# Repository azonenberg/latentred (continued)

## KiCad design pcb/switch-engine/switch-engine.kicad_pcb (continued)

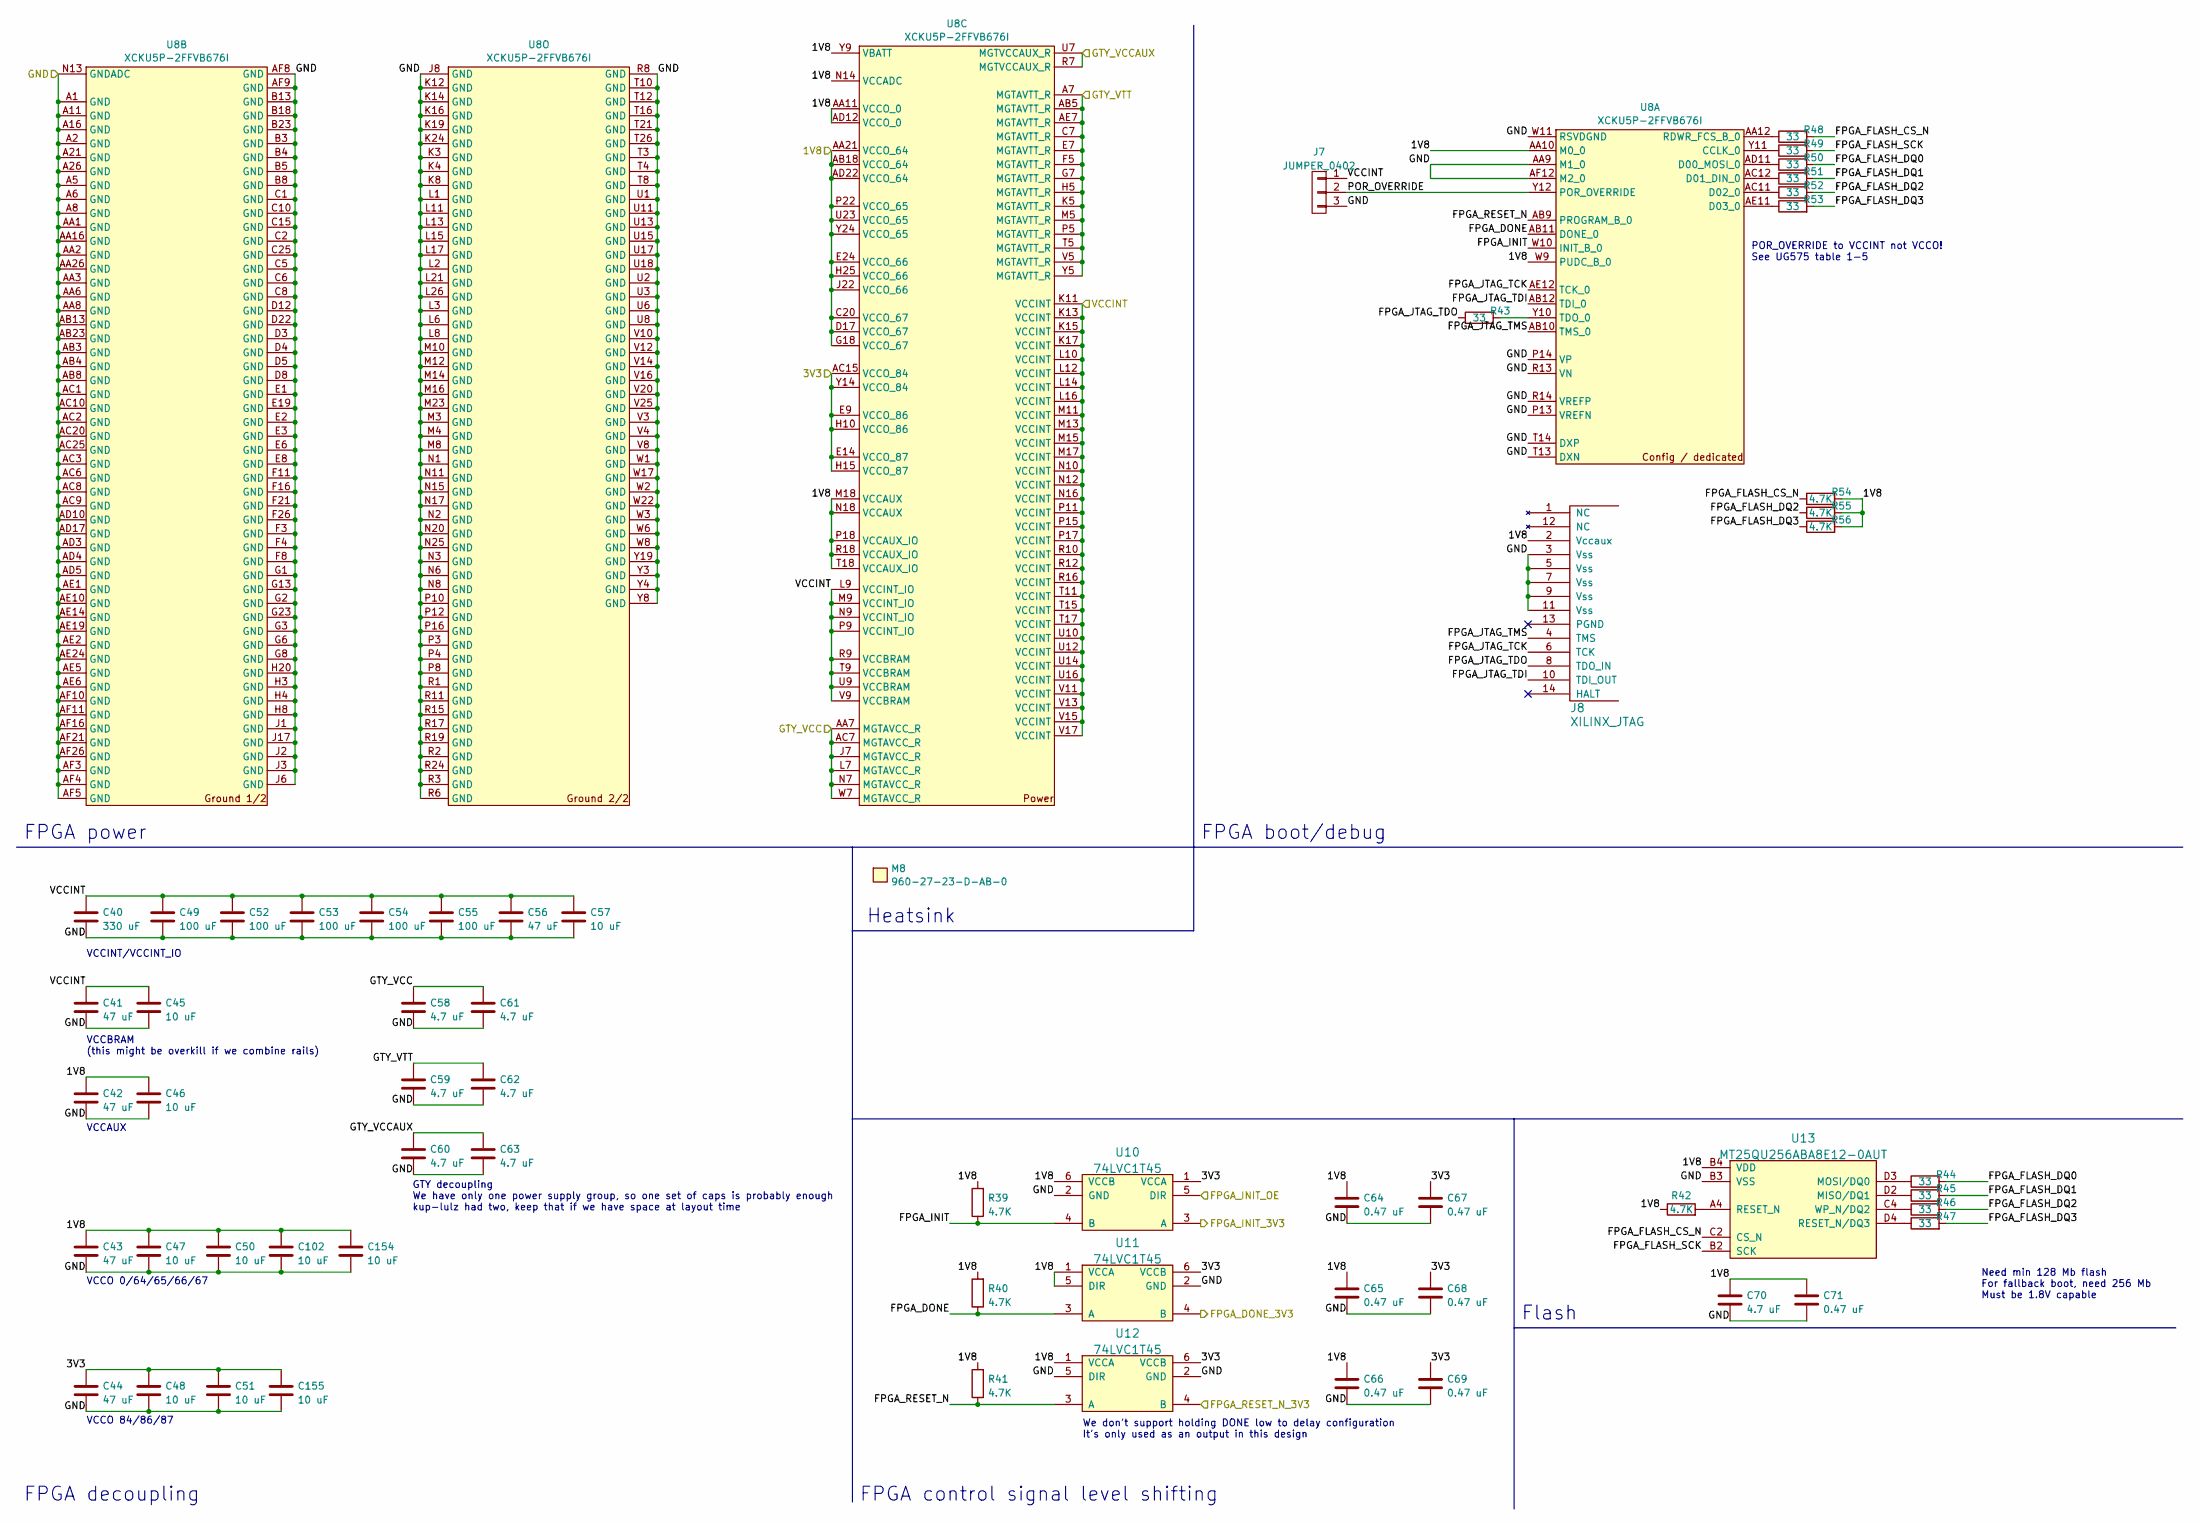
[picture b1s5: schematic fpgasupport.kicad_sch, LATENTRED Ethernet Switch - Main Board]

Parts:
C40: 330 uF; EIA_1210_CAP_NOSILK
C41, C42, C43, C44, C56: 47 uF; EIA_1210_CAP_NOSILK
C45, C46, C47, C48, C50, C51, C57, C102, C154, C155: 10 uF; EIA_0805_CAP_NOSILK
C49, C52, C53, C54, C55: 100 uF; EIA_1210_CAP_NOSILK
C58, C59, C60, C61, C62, C63, C70: 4.7 uF; EIA_0603_CAP_NOSILK
C64, C65, C66, C67, C68, C69, C71: 0.47 uF; EIA_0402_CAP_NOSILK
J7: JUMPER_0402; EIA_0402_JUMPER
J8: XILINX_JTAG; XILINX_JTAG_PTH_MOLEX_0878311420
M8: 960-27-23-D-AB-0; HEATSINK_WAKEFIELDVETTE_960-27-12-D-AB-0
R39, R40, R41, R42, R54, R55, R56: 4.7K; EIA_0402_RES_NOSILK
R43, R44, R45, R46, R47, R48, R49, R50, R51, R52, R53: 33; EIA_0402_RES_NOSILK
U8: XCKU5P-2FFVB676I; BGA_676_27x27_FULLARRAY_1MM_FFG676
U10, U11, U12: 74LVC1T45; DFN_6_0.5MM_1.6x1.6MM_TI_DPK
U13: MT25QU256ABA8E12-0AUT; BGA_24_6x8_DEPOP1_1MM

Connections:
/1V8: C42.1, C43.1, C46.1, C47.1, C50.1, C64.1, C65.1, C66.1, C70.1, C71.1, C102.1, C154.1, J8.2 (Vccaux), R39.2, R40.2, R41.2, R42.1, R54.2, R55.2, R56.2, U8.AA10 (M0_0), U8.AA11 (VCCO_0), U8.AA21 (VCCO_64), U8.AB18 (VCCO_64), U8.AD12 (VCCO_0), U8.AD22 (VCCO_64), U8.C20 (VCCO_67), U8.D17 (VCCO_67), U8.E24 (VCCO_66), U8.G18 (VCCO_67), U8.H25 (VCCO_66), U8.J22 (VCCO_66), U8.M18 (VCCAUX), U8.N14 (VCCADC), U8.N18 (VCCAUX), U8.P18 (VCCAUX_IO), U8.P22 (VCCO_65), U8.R18 (VCCAUX_IO), U8.T18 (VCCAUX_IO), U8.U23 (VCCO_65), U8.W9 (PUDC_B_0), U8.Y9 (VBATT), U8.Y24 (VCCO_65), U10.6 (VCCB), U11.1 (VCCA), U11.5 (DIR), U12.1 (VCCA), U13.B4 (VDD); also elsewhere on the board
/3V3: C44.1, C48.1, C51.1, C67.1, C68.1, C69.1, C155.1, U8.AC15 (VCCO_84), U8.E9 (VCCO_86), U8.E14 (VCCO_87), U8.H10 (VCCO_86), U8.H15 (VCCO_87), U8.Y14 (VCCO_84), U10.1 (VCCA), U11.6 (VCCB), U12.6 (VCCB); also elsewhere on the board
/FPGA support/FPGA_DONE: R40.1, U8.AB11 (DONE_0), U11.3 (A)
/FPGA support/FPGA_DONE_3V3: U11.4 (B); also elsewhere on the board
/FPGA support/FPGA_FLASH_CS_N: R48.2, R54.1, U13.C2 (CS_N)
/FPGA support/FPGA_FLASH_DQ0: R44.2, R50.2
/FPGA support/FPGA_FLASH_DQ1: R45.2, R51.2
/FPGA support/FPGA_FLASH_DQ2: R46.2, R52.2, R55.1
/FPGA support/FPGA_FLASH_DQ3: R47.2, R53.2, R56.1
/FPGA support/FPGA_FLASH_SCK: R49.2, U13.B2 (SCK)
/FPGA support/FPGA_INIT: R39.1, U8.W10 (INIT_B_0), U10.4 (B)
/FPGA support/FPGA_INIT_3V3: U10.3 (A); also elsewhere on the board
/FPGA support/FPGA_INIT_OE: U10.5 (DIR); also elsewhere on the board
/FPGA support/FPGA_JTAG_TCK: J8.6 (TCK), U8.AE12 (TCK_0)
/FPGA support/FPGA_JTAG_TDI: J8.10 (TDI_OUT), U8.AB12 (TDI_0)
/FPGA support/FPGA_JTAG_TDO: J8.8 (TDO_IN), R43.1
/FPGA support/FPGA_JTAG_TMS: J8.4 (TMS), U8.AB10 (TMS_0)
/FPGA support/FPGA_RESET_N: R41.1, U8.AB9 (PROGRAM_B_0), U12.3 (A)
/FPGA support/FPGA_RESET_N_3V3: U12.4 (B); also elsewhere on the board
/FPGA support/GTY_VCC: C58.1, C61.1, U8.AA7 (MGTAVCC_R), U8.AC7 (MGTAVCC_R), U8.J7 (MGTAVCC_R), U8.L7 (MGTAVCC_R), U8.N7 (MGTAVCC_R), U8.W7 (MGTAVCC_R); also elsewhere on the board
/FPGA support/GTY_VCCAUX: C60.1, C63.1, U8.R7 (MGTVCCAUX_R), U8.U7 (MGTVCCAUX_R); also elsewhere on the board
/FPGA support/POR_OVERRIDE: J7.2, U8.Y12 (POR_OVERRIDE)
/FPGA support/VCCINT: C40.1, C41.1, C45.1, C49.1, C52.1, C53.1, C54.1, C55.1, C56.1, C57.1, J7.1, U8.K11 (VCCINT), U8.K13 (VCCINT), U8.K15 (VCCINT), U8.K17 (VCCINT), U8.L9 (VCCINT_IO), U8.L10 (VCCINT), U8.L12 (VCCINT), U8.L14 (VCCINT), U8.L16 (VCCINT), U8.M9 (VCCINT_IO), U8.M11 (VCCINT), U8.M13 (VCCINT), U8.M15 (VCCINT), U8.M17 (VCCINT), U8.N9 (VCCINT_IO), U8.N10 (VCCINT), U8.N12 (VCCINT), U8.N16 (VCCINT), U8.P9 (VCCINT_IO), U8.P11 (VCCINT), U8.P15 (VCCINT), U8.P17 (VCCINT), U8.R9 (VCCBRAM), U8.R10 (VCCINT), U8.R12 (VCCINT), U8.R16 (VCCINT), U8.T9 (VCCBRAM), U8.T11 (VCCINT), U8.T15 (VCCINT), U8.T17 (VCCINT), U8.U9 (VCCBRAM), U8.U10 (VCCINT), U8.U12 (VCCINT), U8.U14 (VCCINT), U8.U16 (VCCINT), U8.V9 (VCCBRAM), U8.V11 (VCCINT), U8.V13 (VCCINT), U8.V15 (VCCINT), U8.V17 (VCCINT); also elsewhere on the board
/GND: C40.2, C41.2, C42.2, C43.2, C44.2, C45.2, C46.2, C47.2, C48.2, C49.2, C50.2, C51.2, C52.2, C53.2, C54.2, C55.2, C56.2, C57.2, C58.2, C59.2, C60.2, C61.2, C62.2, C63.2, C64.2, C65.2, C66.2, C67.2, C68.2, C69.2, C70.2, C71.2, C102.2, C154.2, C155.2, J7.3, J8.3 (Vss), J8.5 (Vss), J8.7 (Vss), J8.9 (Vss), J8.11 (Vss), U8.A1 (GND), U8.A2 (GND), U8.A5 (GND), U8.A6 (GND), U8.A8 (GND), U8.A11 (GND), U8.A16 (GND), U8.A21 (GND), U8.A26 (GND), U8.AA1 (GND), U8.AA2 (GND), U8.AA3 (GND), U8.AA6 (GND), U8.AA8 (GND), U8.AA9 (M1_0), U8.AA16 (GND), U8.AA26 (GND), U8.AB3 (GND), U8.AB4 (GND), U8.AB8 (GND), U8.AB13 (GND), U8.AB23 (GND), U8.AC1 (GND), U8.AC2 (GND), U8.AC3 (GND), U8.AC6 (GND), U8.AC8 (GND), U8.AC9 (GND), U8.AC10 (GND), U8.AC20 (GND), U8.AC25 (GND), U8.AD3 (GND), U8.AD4 (GND), U8.AD5 (GND), U8.AD10 (GND), U8.AD17 (GND), U8.AE1 (GND), U8.AE2 (GND), U8.AE5 (GND), U8.AE6 (GND), U8.AE10 (GND), U8.AE14 (GND), U8.AE19 (GND), U8.AE24 (GND), U8.AF3 (GND), U8.AF4 (GND), U8.AF5 (GND), U8.AF8 (GND), U8.AF9 (GND), U8.AF10 (GND), U8.AF11 (GND), U8.AF12 (M2_0), U8.AF16 (GND), U8.AF21 (GND), U8.AF26 (GND), U8.B3 (GND), U8.B4 (GND), U8.B5 (GND), U8.B8 (GND), U8.B13 (GND), U8.B18 (GND), U8.B23 (GND), U8.C1 (GND), U8.C2 (GND), U8.C5 (GND), U8.C6 (GND), U8.C8 (GND), U8.C10 (GND), U8.C15 (GND), U8.C25 (GND), U8.D3 (GND), U8.D4 (GND), U8.D5 (GND), U8.D8 (GND), U8.D12 (GND), U8.D22 (GND), U8.E1 (GND), U8.E2 (GND), U8.E3 (GND), U8.E6 (GND), U8.E8 (GND), U8.E19 (GND), U8.F3 (GND), U8.F4 (GND), U8.F8 (GND), U8.F11 (GND), U8.F16 (GND), U8.F21 (GND), U8.F26 (GND), U8.G1 (GND), U8.G2 (GND), U8.G3 (GND), U8.G6 (GND), U8.G8 (GND), U8.G13 (GND), U8.G23 (GND), U8.H3 (GND), U8.H4 (GND), U8.H8 (GND), U8.H20 (GND), U8.J1 (GND), U8.J2 (GND), U8.J3 (GND), U8.J6 (GND), U8.J8 (GND), U8.J17 (GND), U8.K3 (GND), U8.K4 (GND), U8.K8 (GND), U8.K12 (GND), U8.K14 (GND), U8.K16 (GND), U8.K19 (GND), U8.K24 (GND), U8.L1 (GND), U8.L2 (GND), U8.L3 (GND), U8.L6 (GND), U8.L8 (GND), U8.L11 (GND), U8.L13 (GND), U8.L15 (GND), U8.L17 (GND), U8.L21 (GND), U8.L26 (GND), U8.M3 (GND), U8.M4 (GND), U8.M8 (GND), U8.M10 (GND), U8.M12 (GND), U8.M14 (GND), U8.M16 (GND), U8.M23 (GND), U8.N1 (GND), U8.N2 (GND), U8.N3 (GND), U8.N6 (GND), U8.N8 (GND), U8.N11 (GND), U8.N13 (GNDADC), U8.N15 (GND), U8.N17 (GND), U8.N20 (GND), U8.N25 (GND), U8.P3 (GND), U8.P4 (GND), U8.P8 (GND), U8.P10 (GND), U8.P12 (GND), U8.P13 (VREFN), U8.P14 (VP), U8.P16 (GND), U8.R1 (GND), U8.R2 (GND), U8.R3 (GND), U8.R6 (GND), U8.R8 (GND), U8.R11 (GND), U8.R13 (VN), U8.R14 (VREFP), U8.R15 (GND), U8.R17 (GND), U8.R19 (GND), U8.R24 (GND), U8.T3 (GND), U8.T4 (GND), U8.T8 (GND), U8.T10 (GND), U8.T12 (GND), U8.T13 (DXN), U8.T14 (DXP), U8.T16 (GND), U8.T21 (GND), U8.T26 (GND), U8.U1 (GND), U8.U2 (GND), U8.U3 (GND), U8.U6 (GND), U8.U8 (GND), U8.U11 (GND), U8.U13 (GND), U8.U15 (GND), U8.U17 (GND), U8.U18 (GND), U8.V3 (GND), U8.V4 (GND), U8.V8 (GND), U8.V10 (GND), U8.V12 (GND), U8.V14 (GND), U8.V16 (GND), U8.V20 (GND), U8.V25 (GND), U8.W1 (GND), U8.W2 (GND), U8.W3 (GND), U8.W6 (GND), U8.W8 (GND), U8.W11 (RSVDGND), U8.W17 (GND), U8.W22 (GND), U8.Y3 (GND), U8.Y4 (GND), U8.Y8 (GND), U8.Y19 (GND), U10.2 (GND), U11.2 (GND), U12.2 (GND), U12.5 (DIR), U13.B3 (VSS); also elsewhere on the board
/GTY_VTT: C59.1, C62.1, U8.A7 (MGTAVTT_R), U8.AB5 (MGTAVTT_R), U8.AE7 (MGTAVTT_R), U8.C7 (MGTAVTT_R), U8.E7 (MGTAVTT_R), U8.F5 (MGTAVTT_R), U8.G7 (MGTAVTT_R), U8.H5 (MGTAVTT_R), U8.K5 (MGTAVTT_R), U8.M5 (MGTAVTT_R), U8.P5 (MGTAVTT_R), U8.T5 (MGTAVTT_R), U8.V5 (MGTAVTT_R), U8.Y5 (MGTAVTT_R); also elsewhere on the board
unnamed: R49.1, U8.Y11 (CCLK_0)
unnamed: R50.1, U8.AD11 (D00_MOSI_0)
unnamed: R51.1, U8.AC12 (D01_DIN_0)
unnamed: R52.1, U8.AC11 (D02_0)
unnamed: R53.1, U8.AE11 (D03_0)
unnamed: R48.1, U8.AA12 (RDWR_FCS_B_0)
unnamed: R43.2, U8.Y10 (TDO_0)
unnamed: R45.1, U13.D2 (MISO/DQ1)
unnamed: R44.1, U13.D3 (MOSI/DQ0)
unnamed: R42.2, U13.A4 (RESET_N)
unnamed: R47.1, U13.D4 (RESET_N/DQ3)
unnamed: R46.1, U13.C4 (WP_N/DQ2)

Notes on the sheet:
FPGA control signal level shifting
FPGA decoupling
FPGA boot/debug
VCCO 0/64/65/66/67
We don't support holding DONE low to delay configuration It's only used as an output in this design
Need min 128 Mb flash For fallback boot, need 256 Mb Must be 1.8V capable
POR_OVERRIDE to VCCINT not VCCO! See UG575 table 1-5
VCCO 84/86/87
FPGA power
VCCBRAM (this might be overkill if we combine rails)
VCCINT/VCCINT_IO
Heatsink
VCCAUX
Flash
GTY decoupling We have only one power supply group, so one set of caps is probably enough kup-lulz had two, keep that if we have space at layout time

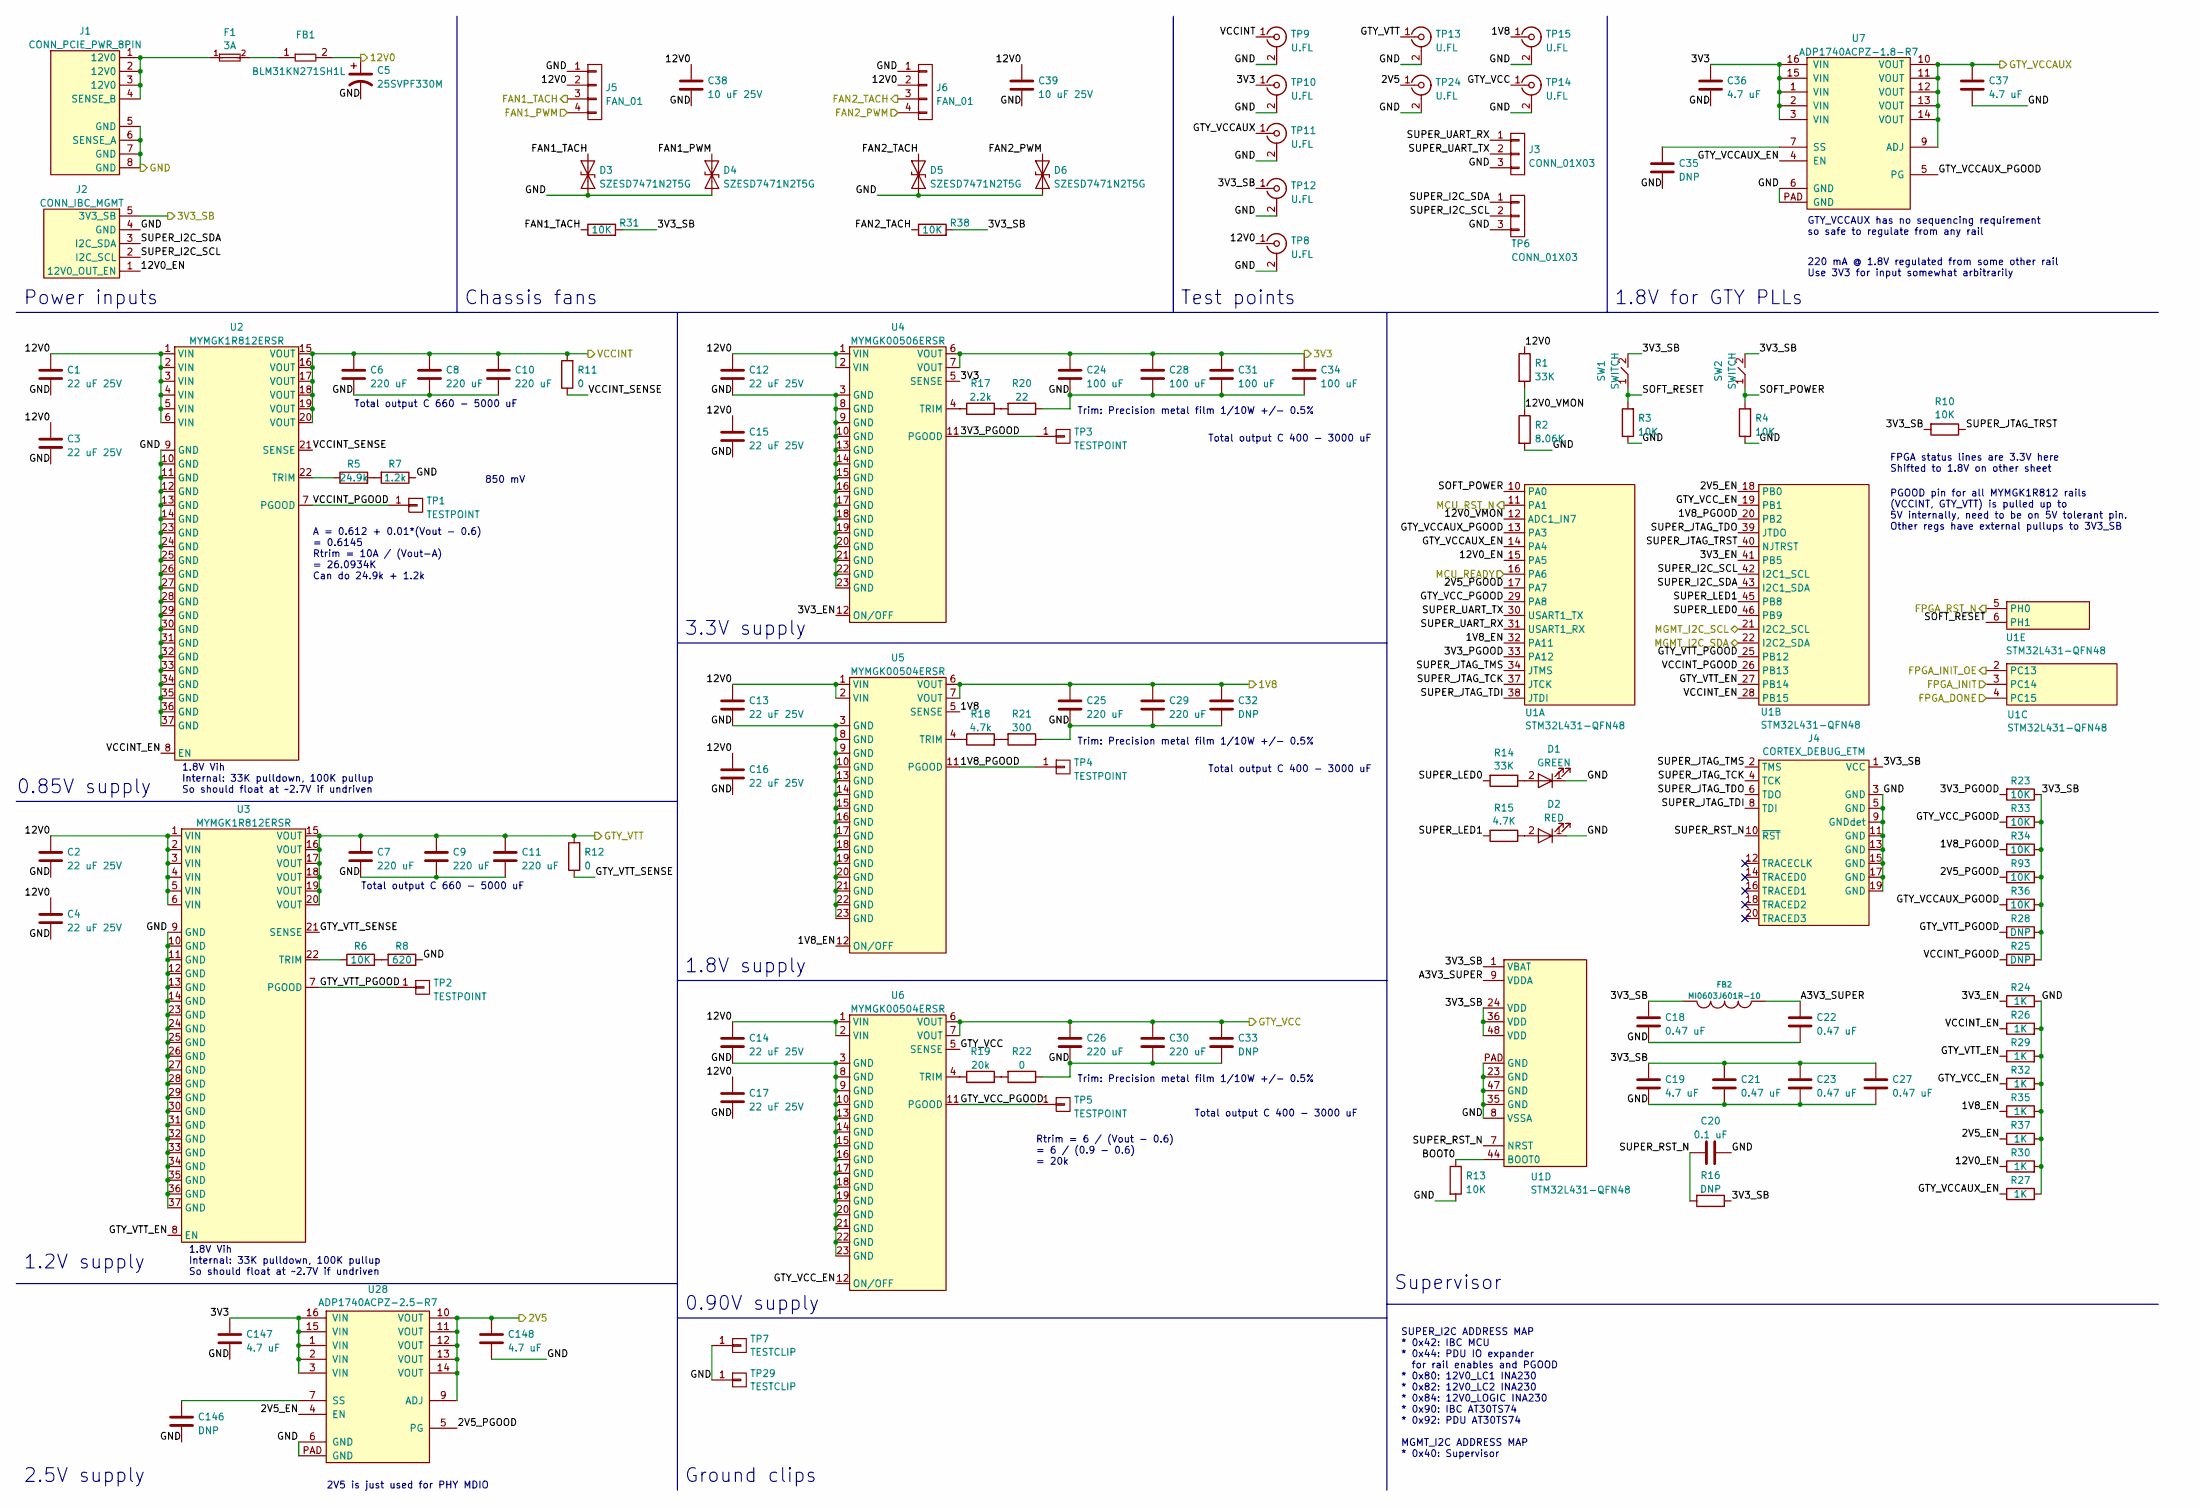
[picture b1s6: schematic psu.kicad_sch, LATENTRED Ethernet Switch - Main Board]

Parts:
C1, C2, C3, C4, C12, C13, C14, C15, C16, C17: 22 uF 25V; EIA_1812_CAP_NOSILK
C5: 25SVPF330M; CAP_AL_10MM_SMT
C6, C7, C8, C9, C10, C11, C25, C26, C29, C30: 220 uF; EIA_1210_CAP_NOSILK
C18, C21, C22, C23, C27: 0.47 uF; EIA_0402_CAP_NOSILK
C19, C36, C37, C147, C148: 4.7 uF; EIA_0603_CAP_NOSILK
C20: 0.1 uF; EIA_0402_CAP_NOSILK
C24, C28, C31, C34: 100 uF; EIA_1210_CAP_NOSILK
C32, C33: DNP; EIA_1210_CAP_NOSILK
C35, C146: DNP; EIA_0402_CAP_NOSILK
C38, C39: 10 uF 25V; EIA_1210_CAP_NOSILK
D1: GREEN; EIA_0402_LED
D2: RED; EIA_0402_LED
D3, D4, D5, D6: SZESD7471N2T5G; SOD882
F1: 3A; EIA_0603_CAP_NOSILK
FB1: BLM31KN271SH1L; EIA_1206_CAP_NOSILK
FB2: MI0603J601R-10; EIA_0603_INDUCTOR_NOSILK
J1: CONN_PCIE_PWR_8PIN; CONN_MOLEX_MINIFITJR_8POS_0039291087
J2: CONN_IBC_MGMT; CONN_MOLEX_PICOBLADE_5POS_0532610571
J3: CONN_01X03; CONN_HEADER_2.54MM_1x3_REFLOW
J4: CORTEX_DEBUG_ETM; CONN_HEADER_1.27MM_2x10_SMT_SAMTEC_FTSH-110-01-L-DV-K
J5, J6: FAN_01; CONN_MOLEX_KK_0470531000
R1, R14: 33K; EIA_0402_RES_NOSILK
R2: 8.06K; EIA_0402_RES_NOSILK
R3, R4, R6, R10, R13, R23, R31, R33, R34, R36, R38, R93: 10K; EIA_0402_RES_NOSILK
R5: 24.9k; EIA_0402_RES_NOSILK
R7: 1.2k; EIA_0402_RES_NOSILK
R8: 620; EIA_0402_RES_NOSILK
R11, R12, R22: 0; EIA_0402_RES_NOSILK
R15: 4.7K; EIA_0402_RES_NOSILK
R16, R25, R28: DNP; EIA_0402_RES_NOSILK
R17: 2.2k; EIA_0402_RES_NOSILK
R18: 4.7k; EIA_0402_RES_NOSILK
R19: 20k; EIA_0402_RES_NOSILK
R20: 22; EIA_0402_RES_NOSILK
R21: 300; EIA_0402_RES_NOSILK
R24, R26, R27, R29, R30, R32, R35, R37: 1K; EIA_0402_RES_NOSILK
SW1, SW2: SWITCH; SWITCH_RAFI_MICON_5
TP1, TP2, TP3, TP4, TP5: TESTPOINT; TESTPOINT_SMT_0.5MM
TP6: CONN_01X03; CONN_HEADER_2.54MM_1x3_REFLOW
TP7, TP29: TESTCLIP; TESTPOINT_SMT_KEYSTONE_5016
TP8, TP9, TP10, TP11, TP12, TP13, TP14, TP15, TP24: U.FL; CONN_U.FL_TE_1909763-1
U1: STM32L431-QFN48; QFN_48_0.5MM_7x7MM
U2, U3: MYMGK1R812ERSR; MODULE_MURATA_MYMGK1R812
U4: MYMGK00506ERSR; MODULE_MURATA_MYMGK00504ERSR
U5, U6: MYMGK00504ERSR; MODULE_MURATA_MYMGK00504ERSR
U7: ADP1740ACPZ-1.8-R7; QFN_16_0.65MM_4x4MM
U28: ADP1740ACPZ-2.5-R7; QFN_16_0.65MM_4x4MM

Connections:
/1V8: C25.1, C29.1, C32.1, TP15.1 (In), U5.5 (SENSE), U5.6 (VOUT), U5.7 (VOUT); also elsewhere on the board
/2V5: C148.1, TP24.1 (In), U28.9 (ADJ), U28.10 (VOUT), U28.11 (VOUT), U28.12 (VOUT), U28.13 (VOUT), U28.14 (VOUT); also elsewhere on the board
/3V3: C24.1, C28.1, C31.1, C34.1, C36.1, C147.1, TP10.1 (In), U4.5 (SENSE), U4.6 (VOUT), U4.7 (VOUT), U7.1 (VIN), U7.2 (VIN), U7.3 (VIN), U7.15 (VIN), U7.16 (VIN), U28.1 (VIN), U28.2 (VIN), U28.3 (VIN), U28.15 (VIN), U28.16 (VIN); also elsewhere on the board
/FPGA support/FPGA_DONE_3V3: U1.4 (PC15); also elsewhere on the board
/FPGA support/FPGA_INIT_3V3: U1.3 (PC14); also elsewhere on the board
/FPGA support/FPGA_INIT_OE: U1.2 (PC13); also elsewhere on the board
/FPGA support/FPGA_RESET_N_3V3: U1.5 (PH0); also elsewhere on the board
/FPGA support/GTY_VCC: C26.1, C30.1, C33.1, TP14.1 (In), U6.5 (SENSE), U6.6 (VOUT), U6.7 (VOUT); also elsewhere on the board
/FPGA support/GTY_VCCAUX: C37.1, TP11.1 (In), U7.9 (ADJ), U7.10 (VOUT), U7.11 (VOUT), U7.12 (VOUT), U7.13 (VOUT), U7.14 (VOUT); also elsewhere on the board
/FPGA support/VCCINT: C6.1, C8.1, C10.1, R11.2, TP9.1 (In), U2.15 (VOUT), U2.16 (VOUT), U2.17 (VOUT), U2.18 (VOUT), U2.19 (VOUT), U2.20 (VOUT); also elsewhere on the board
/GND: C1.2, C2.2, C3.2, C4.2, C5.2, C6.2, C7.2, C8.2, C9.2, C10.2, C11.2, C12.2, C13.2, C14.2, C15.2, C16.2, C17.2, C18.2, C19.2, C20.2, C21.2, C22.2, C23.2, C24.2, C25.2, C26.2, C27.2, C28.2, C29.2, C30.2, C31.2, C32.2, C33.2, C34.2, C35.2, C36.2, C37.2, C38.2, C39.2, C146.2, C147.2, C148.2, D1.1 (K), D2.1 (K), D3.1 (A1), D4.1 (A1), D5.1 (A1), D6.1 (A1), J1.5 (GND), J1.6 (SENSE_A), J1.7 (GND), J1.8 (GND), J2.4 (GND), J3.3, J4.3 (GND), J4.5 (GND), J4.9 (GNDdet), J4.11 (GND), J4.13 (GND), J4.15 (GND), J4.17 (GND), J4.19 (GND), J5.1, J6.1, R2.2, R3.1, R4.1, R7.1, R8.1, R13.2, R20.1, R21.1, R22.1, R24.2, R26.2, R27.2, R29.2, R30.2, R32.2, R35.2, R37.2, TP6.3, TP7.1, TP8.2 (Ext), TP9.2 (Ext), TP10.2 (Ext), TP11.2 (Ext), TP12.2 (Ext), TP13.2 (Ext), TP14.2 (Ext), TP15.2 (Ext), TP24.2 (Ext), TP29.1, U1.8 (VSSA), U1.23 (GND), U1.35 (GND), U1.47 (GND), U1.PAD (GND), U2.9 (GND), U2.10 (GND), U2.11 (GND), U2.12 (GND), U2.13 (GND), U2.14 (GND), U2.23 (GND), U2.24 (GND), U2.25 (GND), U2.26 (GND), U2.27 (GND), U2.28 (GND), U2.29 (GND), U2.30 (GND), U2.31 (GND), U2.32 (GND), U2.33 (GND), U2.34 (GND), U2.35 (GND), U2.36 (GND), U2.37 (GND), U3.9 (GND), U3.10 (GND), U3.11 (GND), U3.12 (GND), U3.13 (GND), U3.14 (GND), U3.23 (GND), U3.24 (GND), U3.25 (GND), U3.26 (GND), U3.27 (GND), U3.28 (GND), U3.29 (GND), U3.30 (GND), U3.31 (GND), U3.32 (GND), U3.33 (GND), U3.34 (GND), U3.35 (GND), U3.36 (GND), U3.37 (GND), U4.3 (GND), U4.8 (GND), U4.9 (GND), U4.10 (GND), U4.13 (GND), U4.14 (GND), U4.15 (GND), U4.16 (GND), U4.17 (GND), U4.18 (GND), U4.19 (GND), U4.20 (GND), U4.21 (GND), U4.22 (GND), U4.23 (GND), U5.3 (GND), U5.8 (GND), U5.9 (GND), U5.10 (GND), U5.13 (GND), U5.14 (GND), U5.15 (GND), U5.16 (GND), U5.17 (GND), U5.18 (GND), U5.19 (GND), U5.20 (GND), U5.21 (GND), U5.22 (GND), U5.23 (GND), U6.3 (GND), U6.8 (GND), U6.9 (GND), U6.10 (GND), U6.13 (GND), U6.14 (GND), U6.15 (GND), U6.16 (GND), U6.17 (GND), U6.18 (GND), U6.19 (GND), U6.20 (GND), U6.21 (GND), U6.22 (GND), U6.23 (GND), U7.6 (GND), U7.PAD (GND), U28.6 (GND), U28.PAD (GND); also elsewhere on the board
/GTY_VTT: C7.1, C9.1, C11.1, R12.2, TP13.1 (In), U3.15 (VOUT), U3.16 (VOUT), U3.17 (VOUT), U3.18 (VOUT), U3.19 (VOUT), U3.20 (VOUT); also elsewhere on the board
/MCU/3V3_SB: C18.1, C19.1, C21.1, C23.1, C27.1, FB2.2, J2.5 (3V3_SB), J4.1 (VCC), R10.2, R16.1, R23.1, R25.2, R28.2, R31.2, R33.1, R34.1, R36.2, R38.2, R93.2, SW1.2, SW2.2, TP12.1 (In), U1.1 (VBAT), U1.24 (VDD), U1.36 (VDD), U1.48 (VDD); also elsewhere on the board
/MCU/MCU_READY: U1.16 (PA6); also elsewhere on the board
/MCU/MCU_RST_N: U1.11 (PA1); also elsewhere on the board
/MCU/MGMT_I2C_SCL: U1.21 (I2C2_SCL); also elsewhere on the board
/MCU/MGMT_I2C_SDA: U1.22 (I2C2_SDA); also elsewhere on the board
/Power Supply/1V8_EN: R35.1, U1.32 (PA11), U5.12 (ON/OFF)
/Power Supply/1V8_PGOOD: R34.2, TP4.1, U1.20 (PB2), U5.11 (PGOOD)
/Power Supply/2V5_EN: R37.1, U1.18 (PB0), U28.4 (EN)
/Power Supply/2V5_PGOOD: R93.1, U1.17 (PA7), U28.5 (PG)
/Power Supply/3V3_EN: R24.1, U1.41 (PB5), U4.12 (ON/OFF)
/Power Supply/3V3_PGOOD: R23.2, TP3.1, U1.33 (PA12), U4.11 (PGOOD)
/Power Supply/12V0: C1.1, C2.1, C3.1, C4.1, C5.1, C12.1, C13.1, C14.1, C15.1, C16.1, C17.1, C38.1, C39.1, FB1.2, J5.2, J6.2, R1.1, TP8.1 (In), U2.1 (VIN), U2.2 (VIN), U2.3 (VIN), U2.4 (VIN), U2.5 (VIN), U2.6 (VIN), U3.1 (VIN), U3.2 (VIN), U3.3 (VIN), U3.4 (VIN), U3.5 (VIN), U3.6 (VIN), U4.1 (VIN), U4.2 (VIN), U5.1 (VIN), U5.2 (VIN), U6.1 (VIN), U6.2 (VIN)
/Power Supply/12V0_EN: J2.1 (12V0_OUT_EN), R30.1, U1.15 (PA5)
/Power Supply/12V0_VMON: R1.2, R2.1, U1.12 (ADC1_IN7)
/Power Supply/A3V3_SUPER: C22.1, FB2.1, U1.9 (VDDA)
/Power Supply/BOOT0: R13.1, U1.44 (BOOT0)
/Power Supply/FAN1_PWM: D4.2 (A2), J5.4; also elsewhere on the board
/Power Supply/FAN1_TACH: D3.2 (A2), J5.3, R31.1; also elsewhere on the board
/Power Supply/FAN2_PWM: D6.2 (A2), J6.4; also elsewhere on the board
/Power Supply/FAN2_TACH: D5.2 (A2), J6.3, R38.1; also elsewhere on the board
/Power Supply/GTY_VCCAUX_EN: R27.1, U1.14 (PA4), U7.4 (EN)
/Power Supply/GTY_VCCAUX_PGOOD: R36.1, U1.13 (PA3), U7.5 (PG)
/Power Supply/GTY_VCC_EN: R32.1, U1.19 (PB1), U6.12 (ON/OFF)
/Power Supply/GTY_VCC_PGOOD: R33.2, TP5.1, U1.29 (PA8), U6.11 (PGOOD)
/Power Supply/GTY_VTT_EN: R29.1, U1.27 (PB14), U3.8 (EN)
/Power Supply/GTY_VTT_PGOOD: R28.1, TP2.1, U1.25 (PB12), U3.7 (PGOOD)
/Power Supply/GTY_VTT_SENSE: R12.1, U3.21 (SENSE)
/Power Supply/SOFT_POWER: R4.2, SW2.1, U1.10 (PA0)
/Power Supply/SOFT_RESET: R3.2, SW1.1, U1.6 (PH1)
/Power Supply/SUPER_I2C_SCL: J2.2 (I2C_SCL), TP6.2, U1.42 (I2C1_SCL)
/Power Supply/SUPER_I2C_SDA: J2.3 (I2C_SDA), TP6.1, U1.43 (I2C1_SDA)
/Power Supply/SUPER_JTAG_TCK: J4.4 (TCK), U1.37 (JTCK)
/Power Supply/SUPER_JTAG_TDI: J4.8 (TDI), U1.38 (JTDI)
/Power Supply/SUPER_JTAG_TDO: J4.6 (TDO), U1.39 (JTDO)
/Power Supply/SUPER_JTAG_TMS: J4.2 (TMS), U1.34 (JTMS)
/Power Supply/SUPER_JTAG_TRST: R10.1, U1.40 (NJTRST)
/Power Supply/SUPER_LED0: R14.2, U1.46 (PB9)
/Power Supply/SUPER_LED1: R15.2, U1.45 (PB8)
/Power Supply/SUPER_RST_N: C20.1, J4.10 (~RST), R16.2, U1.7 (NRST)
/Power Supply/SUPER_UART_RX: J3.1, U1.31 (USART1_RX)
/Power Supply/SUPER_UART_TX: J3.2, U1.30 (USART1_TX)
/Power Supply/VCCINT_EN: R26.1, U1.28 (PB15), U2.8 (EN)
/Power Supply/VCCINT_PGOOD: R25.1, TP1.1, U1.26 (PB13), U2.7 (PGOOD)
/Power Supply/VCCINT_SENSE: R11.1, U2.21 (SENSE)
unnamed: D1.2 (A), R14.1
unnamed: D2.2 (A), R15.1
unnamed: F1.2, FB1.1
unnamed: F1.1, J1.1 (12V0), J1.2 (12V0), J1.3 (12V0), J1.4 (SENSE_B)
unnamed: R5.2, R7.2
unnamed: R6.2, R8.2
unnamed: R17.2, R20.2
unnamed: R18.2, R21.2
unnamed: R19.2, R22.2
unnamed: R5.1, U2.22 (TRIM)
unnamed: R6.1, U3.22 (TRIM)
unnamed: R17.1, U4.4 (TRIM)
unnamed: R18.1, U5.4 (TRIM)
unnamed: R19.1, U6.4 (TRIM)
unnamed: C35.1, U7.7 (SS)
unnamed: C146.1, U28.7 (SS)

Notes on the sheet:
A = 0.612 + 0.01*(Vout - 0.6) = 0.6145 Rtrim = 10A / (Vout-A) = 26.0934K Can do 24.9k + 1.2k
2.5V supply
FPGA status lines are 3.3V here Shifted to 1.8V on other sheet
0.85V supply
Ground clips
Rtrim = 6 / (Vout - 0.6) = 6 / (0.9 - 0.6) = 20k
Supervisor
Test points
Total output C 400 - 3000 uF
220 mA @ 1.8V regulated from some other rail Use 3V3 for input somewhat arbitrarily
0.90V supply
850 mV
1.8V supply
1.8V for GTY PLLs
1.8V Vih Internal: 33K pulldown, 100K pullup So should float at ~2.7V if undriven
3.3V supply
Total output C 660 - 5000 uF
Power inputs
PGOOD pin for all MYMGK1R812 rails (VCCINT, GTY_VTT) is pulled up to 5V internally, need to be on 5V tolerant pin. Other regs have external pullups to 3V3_SB
Trim: Precision metal film 1/10W +/- 0.5%
2V5 is just used for PHY MDIO
Chassis fans
SUPER_I2C ADDRESS MAP * 0x42: IBC MCU * 0x44: PDU IO expander for rail enables and PGOOD * 0x80: 12V0_LC1 INA230 * 0x82: 12V0_LC2 INA230 * 0x84: 12V0_LOGIC INA230 * 0x90: IBC AT30TS74 * 0x92: PDU AT30TS74 MGMT_I2C ADDRESS MAP * 0x40: Supervisor
GTY_VCCAUX has no sequencing requirement so safe to regulate from any rail
1.2V supply
